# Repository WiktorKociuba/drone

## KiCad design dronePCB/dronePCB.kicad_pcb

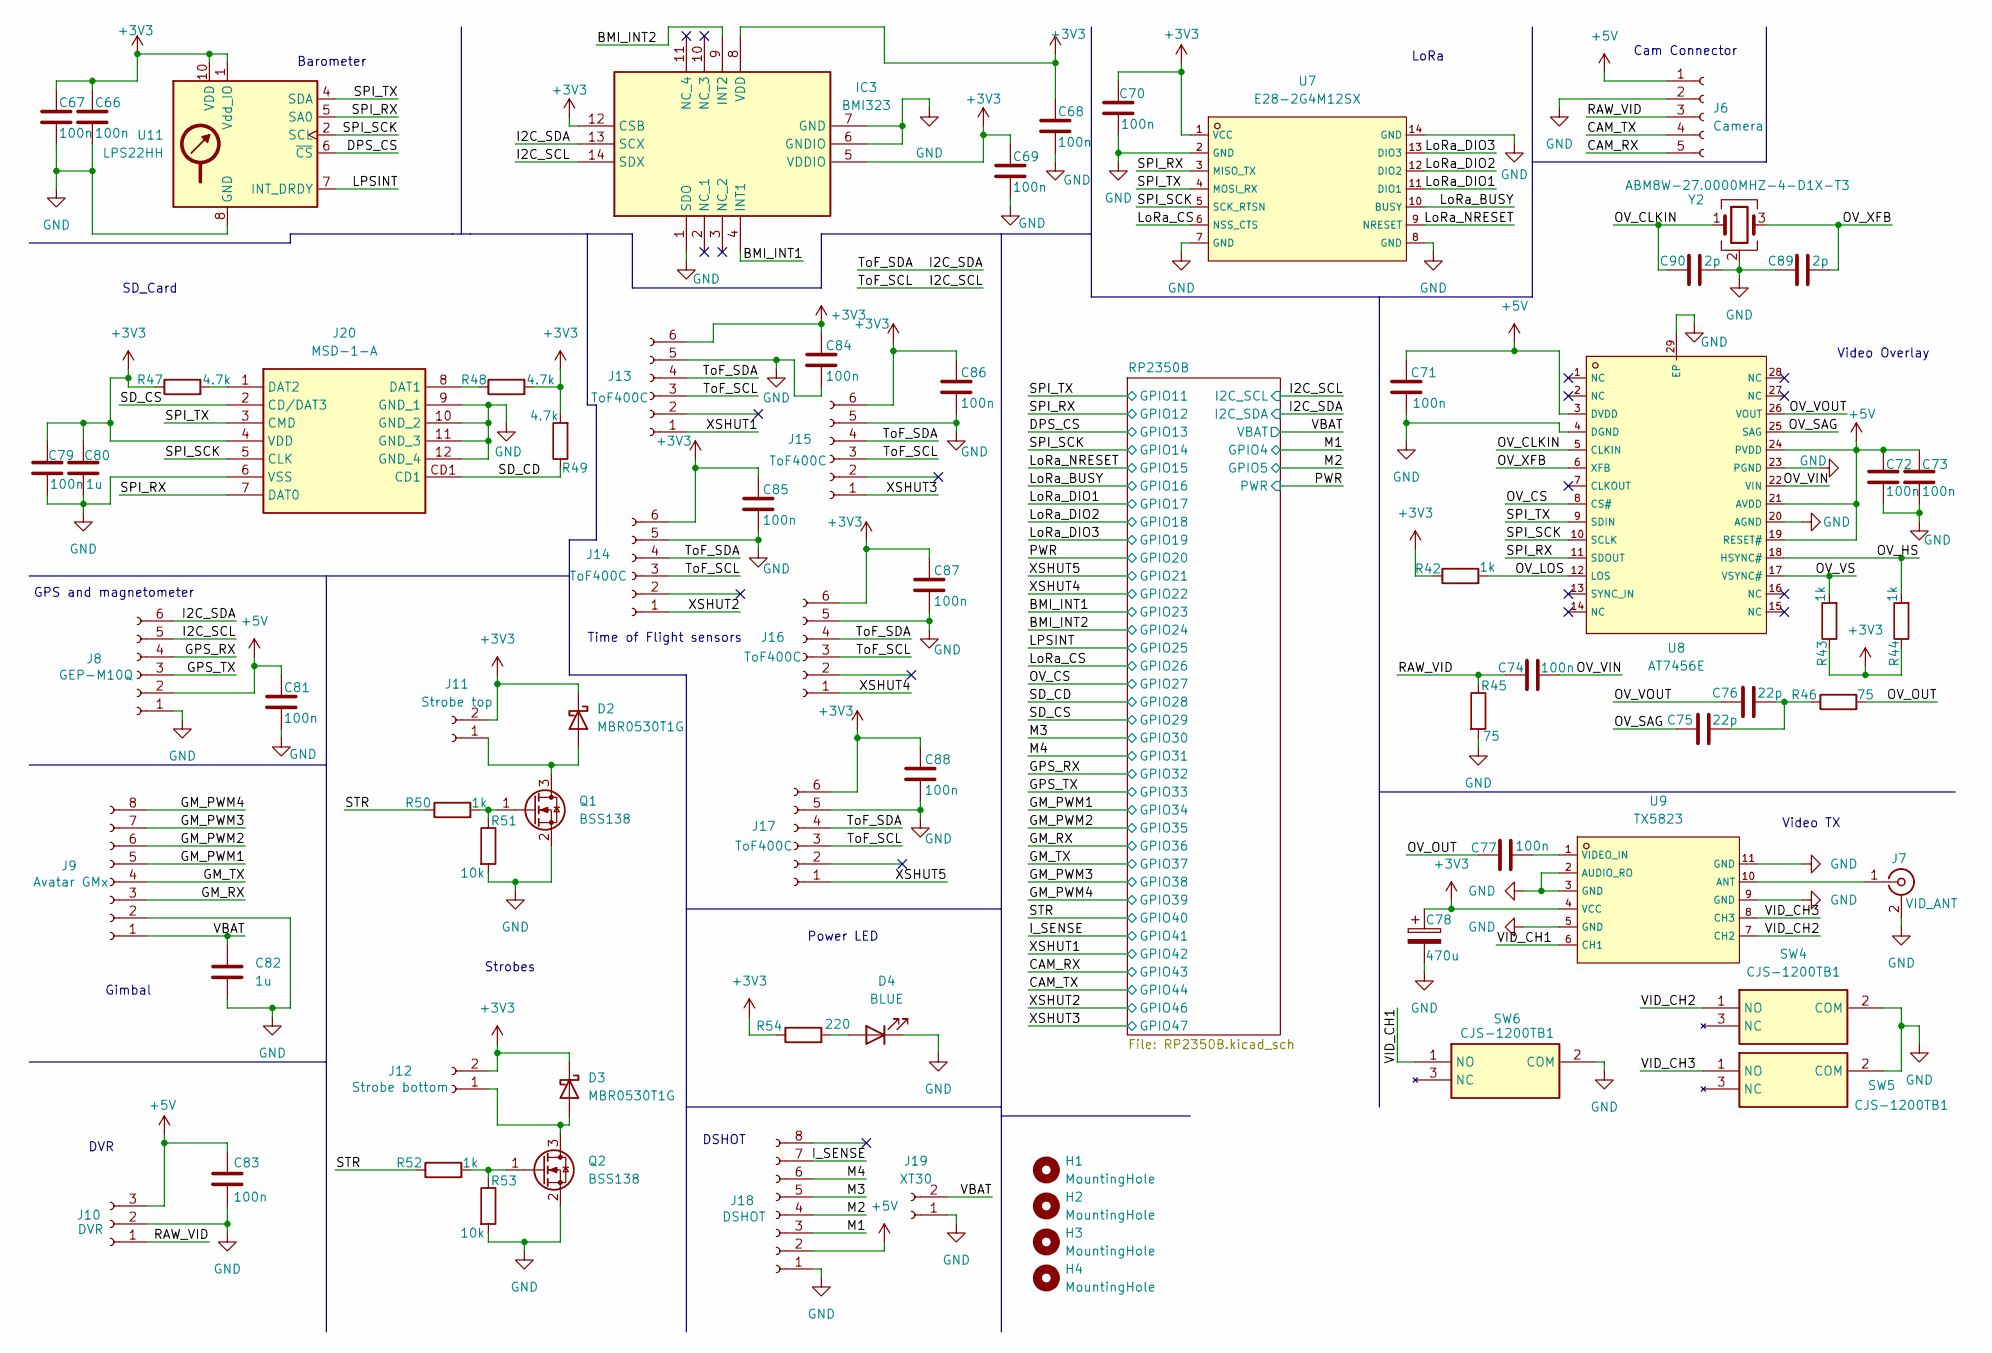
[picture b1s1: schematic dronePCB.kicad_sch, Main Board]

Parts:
C66, C67, C68, C69, C70, C71, C72, C73, C74, C77, C79, C81, C83, C84, C85, C86, C87, C88: 100n; C_0805_2012Metric_Pad1.18x1.45mm_HandSolder; Manufacturer_Part_Number 08056D104KAT2A
C75, C76: 22p; C_0805_2012Metric_Pad1.18x1.45mm_HandSolder; Manufacturer_Part_Number 0805N220J500CT
C78: 470u; CAPAE830X1080N; Manufacturer_Part_Number UCW1C471MNL1GS
C80, C82: 1u; C_0805_2012Metric_Pad1.18x1.45mm_HandSolder; Manufacturer_Part_Number CL21B105KAFNNNG
C89, C90: 2p; C_0805_2012Metric_Pad1.18x1.45mm_HandSolder; Manufacturer_Part_Number 0805N2R0C500CT
D2, D3: MBR0530T1G; D_SOD-123; Manufacturer_Part_Number MBR0530T1G
D4: BLUE; LED_0805_2012Metric_Pad1.15x1.40mm_HandSolder; Manufacturer_Part_Number 150080BS75000
H1, H2, H3, H4: MountingHole; MountingHole_2.2mm_M2; Manufacturer_Part_Number n/a
IC3: BMI323; Mouser Part Number 262-BMI323
J6: Camera; JST_PH_B5B-PH-SM4-TB_1x05-1MP_P2.00mm_Vertical; Manufacturer_Part_Number B5B-PH-SM4-TB(LF)(SN)
J7: VID_ANT; SMA_Amphenol_132134-11_Vertical; Manufacturer_Part_Number n/a
J8: GEP-M10Q; JST_PH_B6B-PH-SM4-TB_1x06-1MP_P2.00mm_Vertical; Manufacturer_Part_Number B6B-PH-SM4-TB(LF)(SN)
J9: Avatar GMx; JST_PH_B8B-PH-SM4-TB_1x08-1MP_P2.00mm_Vertical; Manufacturer_Part_Number B8B-PH-SM4-TBT(LF)(SN)
J10: DVR; JST_PH_B3B-PH-SM4-TB_1x03-1MP_P2.00mm_Vertical; Manufacturer_Part_Number B3B-PH-SM4-TB(LF)(SN)
J11: Strobe top; JST_PH_B2B-PH-SM4-TB_1x02-1MP_P2.00mm_Vertical; Manufacturer_Part_Number B2B-PH-SM4-TB(LF)(SN)
J12: Strobe bottom; JST_PH_B2B-PH-SM4-TB_1x02-1MP_P2.00mm_Vertical; Manufacturer_Part_Number B2B-PH-SM4-TB(LF)(SN)
J13, J14, J15, J16, J17: ToF400C; JST_PH_B6B-PH-SM4-TB_1x06-1MP_P2.00mm_Vertical; Manufacturer_Part_Number B6B-PH-SM4-TB(LF)(SN)
J18: DSHOT; JST_PH_B8B-PH-SM4-TB_1x08-1MP_P2.00mm_Vertical; Manufacturer_Part_Number B8B-PH-SM4-TBT(LF)(SN)
J19: XT30; AMASS_XT30U-F_1x02_P5.0mm_Vertical; Manufacturer_Part_Number XT30U-F AMASS
J20: MSD-1-A; MSD1A; Mouser Part Number 179-MSD-1-A
Q1, Q2: BSS138; SOT-23; Manufacturer_Part_Number BSS138
R42, R43, R44, R50, R52: 1k; R_0805_2012Metric_Pad1.20x1.40mm_HandSolder; Manufacturer_Part_Number CRM0805-FX-1001ELF
R45, R46: 75; R_0805_2012Metric_Pad1.20x1.40mm_HandSolder; Manufacturer_Part_Number CRCW080575R0FKEA
R47, R48, R49: 4.7k; R_0805_2012Metric_Pad1.20x1.40mm_HandSolder; Manufacturer_Part_Number RG2012P-472-B-T5
R51, R53: 10k; R_0805_2012Metric_Pad1.20x1.40mm_HandSolder; Manufacturer_Part_Number CRM0805-FX-1002ELF
R54: 220; R_0805_2012Metric_Pad1.20x1.40mm_HandSolder; Manufacturer_Part_Number CRCW0805220RFKEA
SW4, SW5, SW6: CJS-1200TB1; CJS1200TB1; Mouser Part Number 229-CJS-1200TB1
U7: E28-2G4M12SX; COMM-SMD_E28-2G4M12SX; Manufacturer_Part_Number E28-2G4M12SX; LCSC C17916848
U8: AT7456E; Manufacturer_Part_Number AT7456E; LCSC C82351
U9: TX5823; Manufacturer_Part_Number TX5823; LCSC C2908188
U11: LPS22HH; ST_HLGA-10_2x2mm_P0.5mm_LayoutBorder3x2y; Manufacturer_Part_Number LPS22HBTR
Y2: ABM8W-27.0000MHZ-4-D1X-T3; ABM8W480000MHZ6D1XT3; Manufacturer_Part_Number ABM8W-27.0000MHZ-4-D1X-T3

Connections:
+3V3: C66.1, C67.1, C68.1, C69.1, C70.1, C78.1, C79.1, C80.1, C84.1, C85.1, C86.1, C87.1, C88.1, D2.1 (K), D3.1 (K), IC3.5 (VDDIO), IC3.8 (VDD), IC3.12 (CSB), J11.2, J12.2, J13.6, J14.6, J15.6, J16.6, J17.6, J20.4 (VDD), R42.1, R43.1, R44.1, R47.1, R48.2, R49.2, R54.1, U7.1 (VCC), U9.4 (VCC), U11.1 (Vdd_IO), U11.10 (VDD); also elsewhere on the board
+5V: C71.1, C72.1, C73.1, C81.1, C83.1, J6.1, J8.2, J10.3, J18.2, U8.3 (DVDD), U8.19 (RESET#), U8.21 (AVDD), U8.24 (PVDD); also elsewhere on the board
/BMI_INT1: IC3.4 (INT1); also elsewhere on the board
/BMI_INT2: IC3.9 (INT2); also elsewhere on the board
/CAM_RX: J6.5; also elsewhere on the board
/CAM_TX: J6.4; also elsewhere on the board
/DPS_CS: U11.6 (~CS); also elsewhere on the board
/GM_PWM1: J9.5; also elsewhere on the board
/GM_PWM2: J9.6; also elsewhere on the board
/GM_PWM3: J9.7; also elsewhere on the board
/GM_PWM4: J9.8; also elsewhere on the board
/GM_RX: J9.3; also elsewhere on the board
/GM_TX: J9.4; also elsewhere on the board
/GPS_RX: J8.4; also elsewhere on the board
/GPS_TX: J8.3; also elsewhere on the board
/I2C_SCL: IC3.14 (SDX), J8.5, J13.3, J14.3, J15.3, J16.3, J17.3; also elsewhere on the board
/I2C_SDA: IC3.13 (SCX), J8.6, J13.4, J14.4, J15.4, J16.4, J17.4; also elsewhere on the board
/I_SENSE: J18.7; also elsewhere on the board
/LPSINT: U11.7 (INT_DRDY); also elsewhere on the board
/LoRa_BUSY: U7.10 (BUSY); also elsewhere on the board
/LoRa_CS: U7.6 (NSS_CTS); also elsewhere on the board
/LoRa_DIO1: U7.11 (DIO1); also elsewhere on the board
/LoRa_DIO2: U7.12 (DIO2); also elsewhere on the board
/LoRa_DIO3: U7.13 (DIO3); also elsewhere on the board
/LoRa_NRESET: U7.9 (NRESET); also elsewhere on the board
/M1: J18.3; also elsewhere on the board
/M2: J18.4; also elsewhere on the board
/M3: J18.5; also elsewhere on the board
/M4: J18.6; also elsewhere on the board
/OV_CLKIN: C90.1, U8.5 (CLKIN), Y2.1
/OV_CS: U8.8 (CS#); also elsewhere on the board
/OV_HS: R44.2, U8.18 (HSYNC#)
/OV_LOS: R42.2, U8.12 (LOS)
/OV_OUT: C77.1, R46.2
/OV_SAG: C75.1, U8.25 (SAG)
/OV_VIN: C74.2, U8.22 (VIN)
/OV_VOUT: C76.1, U8.26 (VOUT)
/OV_VS: R43.2, U8.17 (VSYNC#)
/OV_XFB: C89.2, U8.6 (XFB), Y2.3
/RAW_VID: C74.1, J6.3, J10.1, R45.1
/SD_CD: J20.CD1, R49.1; also elsewhere on the board
/SD_CS: J20.2 (CD/DAT3); also elsewhere on the board
/SPI_RX: J20.7 (DAT0), U7.3 (MISO_TX), U8.11 (SDOUT), U11.5 (SA0); also elsewhere on the board
/SPI_SCK: J20.5 (CLK), U7.5 (SCK_RTSN), U8.10 (SCLK), U11.2 (SCL); also elsewhere on the board
/SPI_TX: J20.3 (CMD), U7.4 (MOSI_RX), U8.9 (SDIN), U11.4 (SDA); also elsewhere on the board
/STR: R50.1, R52.1; also elsewhere on the board
/VBAT: C82.1, J9.1, J19.2; also elsewhere on the board
/VID_CH1: SW6.1 (NO), U9.6 (CH1)
/VID_CH2: SW4.1 (NO), U9.7 (CH2)
/VID_CH3: SW5.1 (NO), U9.8 (CH3)
/XSHUT1: J13.1; also elsewhere on the board
/XSHUT2: J14.1; also elsewhere on the board
/XSHUT3: J15.1; also elsewhere on the board
/XSHUT4: J16.1; also elsewhere on the board
/XSHUT5: J17.1; also elsewhere on the board
GND: C66.2, C67.2, C68.2, C69.2, C70.2, C71.2, C72.2, C73.2, C78.2, C79.2, C80.2, C81.2, C82.2, C83.2, C84.2, C85.2, C86.2, C87.2, C88.2, C89.1, C90.2, D4.1 (K), IC3.1 (SDO), IC3.6 (GNDIO), IC3.7 (GND), J6.2, J7.2 (Ext), J8.1, J9.2, J10.2, J13.5, J14.5, J15.5, J16.5, J17.5, J18.1, J19.1, J20.6 (VSS), J20.9 (GND_1), J20.10 (GND_2), J20.11 (GND_3), J20.12 (GND_4), Q1.2 (S), Q2.2 (S), R45.2, R51.2, R53.2, SW4.2 (COM), SW5.2 (COM), SW6.2 (COM), U7.2 (GND), U7.7 (GND), U7.8 (GND), U7.14 (GND), U8.4 (DGND), U8.20 (AGND), U8.23 (PGND), U8.29 (EP), U9.2 (AUDIO_RO), U9.3 (GND), U9.5 (GND), U9.9 (GND), U9.11 (GND), U11.3 (GND), U11.8 (GND), U11.9 (GND), Y2.2 (G), Y2.4 (G); also elsewhere on the board
unnamed: C75.2, C76.2, R46.1
unnamed: D2.2 (A), J11.1, Q1.3 (D)
unnamed: D3.2 (A), J12.1, Q2.3 (D)
unnamed: D4.2 (A), R54.2
unnamed: J7.1 (In), U9.10 (ANT)
unnamed: J20.8 (DAT1), R48.1
unnamed: J20.1 (DAT2), R47.2
unnamed: Q1.1 (G), R50.2, R51.1
unnamed: Q2.1 (G), R52.2, R53.1
unnamed: C77.2, U9.1 (VIDEO_IN)

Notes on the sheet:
Video Overlay
Strobes
DVR
Gimbal
GPS and magnetometer
Power LED
Time of Flight sensors
LoRa
Cam Connector
Barometer
SD_Card
DSHOT
Video TX

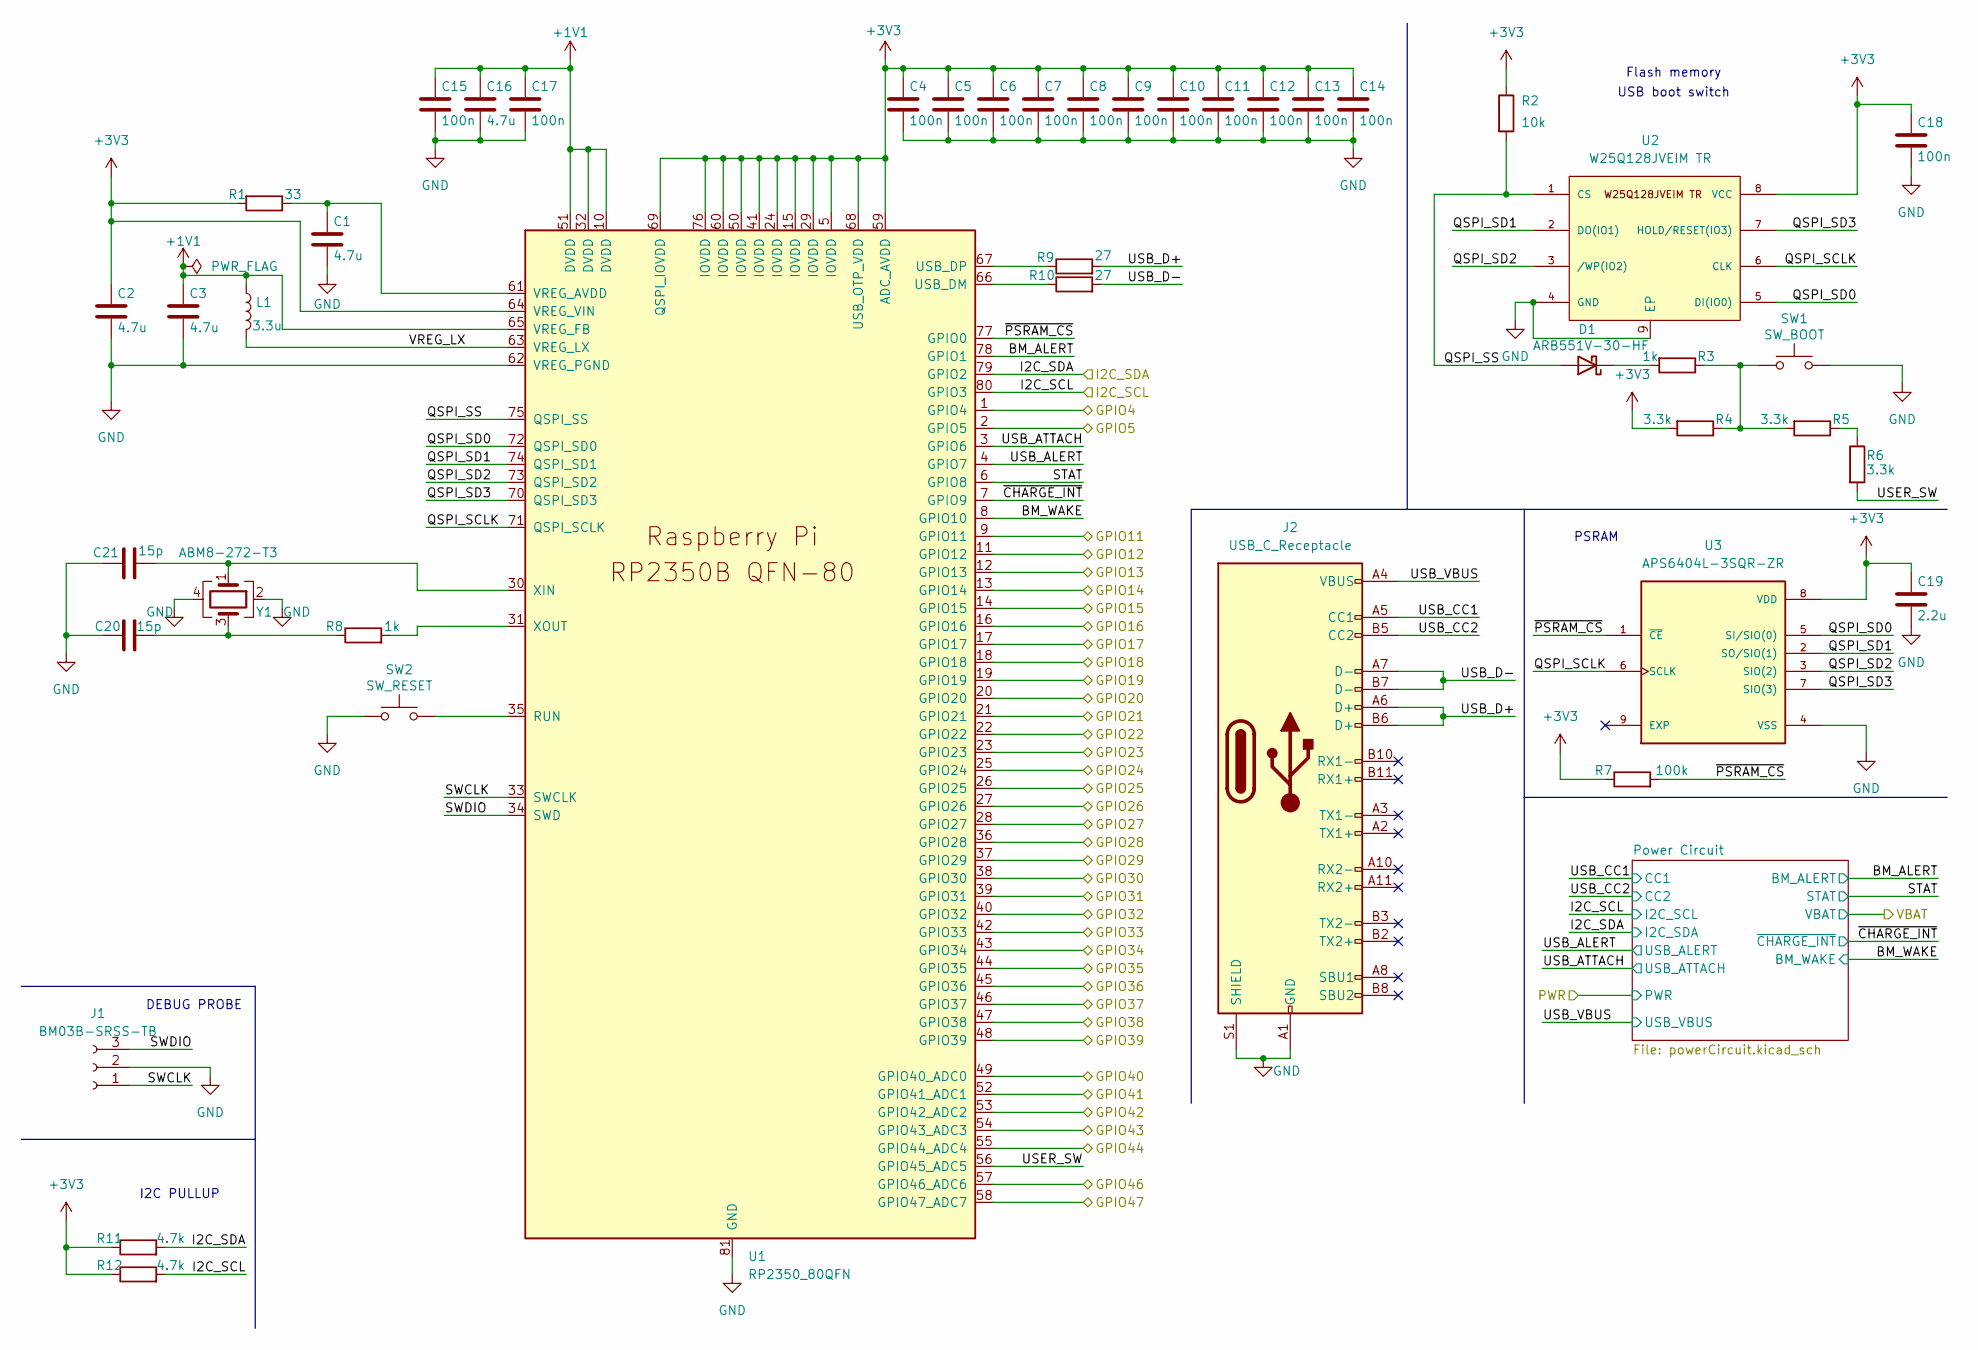
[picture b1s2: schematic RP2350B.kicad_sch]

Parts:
C1, C16: 4.7u; C_0805_2012Metric_Pad1.18x1.45mm_HandSolder; Manufacturer_Part_Number CL21A475KPFNNNF
C2, C3: 4.7u; C_0402_1005Metric_Pad0.74x0.62mm_HandSolder; Manufacturer_Part_Number CL05A475KQ5NRNC
C4, C5, C6, C7, C8, C9, C10, C11, C12, C13, C14, C15, C17, C18: 100n; C_0805_2012Metric_Pad1.18x1.45mm_HandSolder; Manufacturer_Part_Number 08056D104KAT2A
C19: 2.2u; C_0805_2012Metric_Pad1.18x1.45mm_HandSolder; Manufacturer_Part_Number CL21B225KPFNNNE
C20, C21: 15p; C_0805_2012Metric_Pad1.18x1.45mm_HandSolder; Manufacturer_Part_Number C0805C150K1HACTU
D1: ARB551V-30-HF; D_SOD-323_HandSoldering; Manufacturer_Part_Number ARB551V-30-HF
J1: BM03B-SRSS-TB; JST_SH_BM03B-SRSS-TB_1x03-1MP_P1.00mm_Vertical; Manufacturer_Part_Number BM03B-SRSS-TB
J2: USB_C_Receptacle; USB_C_Receptacle_Amphenol_12401610E4-2A; Manufacturer_Part_Number 12401610E4#2A
L1: 3.3u; AOTAB201610S3R3101T; Manufacturer_Part_Number AOTA-B201610S3R3-101-T
R1: 33; R_0805_2012Metric_Pad1.20x1.40mm_HandSolder; Manufacturer_Part_Number CRCW080533R0JNEA
R2: 10k; R_0805_2012Metric_Pad1.20x1.40mm_HandSolder; Manufacturer_Part_Number CRM0805-FX-1002ELF
R3, R8: 1k; R_0805_2012Metric_Pad1.20x1.40mm_HandSolder; Manufacturer_Part_Number CRM0805-FX-1001ELF
R4, R5, R6: 3.3k; R_0805_2012Metric_Pad1.20x1.40mm_HandSolder; Manufacturer_Part_Number SG73S2ARTTD3301F
R7: 100k; R_0805_2012Metric_Pad1.20x1.40mm_HandSolder; Manufacturer_Part_Number CR0805AFX-1003EAS
R9, R10: 27; R_0805_2012Metric_Pad1.20x1.40mm_HandSolder; Manufacturer_Part_Number CRCW080527R0FKEA
R11, R12: 4.7k; R_0805_2012Metric_Pad1.20x1.40mm_HandSolder; Manufacturer_Part_Number RG2012P-472-B-T5
SW1: SW_BOOT; SW_Push_1P1T_NO_Vertical_Wuerth_434133025816; Manufacturer_Part_Number 434133025816
SW2: SW_RESET; SW_Push_1P1T_NO_Vertical_Wuerth_434133025816; Manufacturer_Part_Number 434133025816
U1: RP2350_80QFN; RP2350B; Manufacturer_Part_Number SC1510(13)-A4
U2: W25Q128JVEIM TR; SON127P800X600X80-9N-D; Manufacturer_Part_Number W25Q128JVEIM TR
U3: APS6404L-3SQR-ZR; PSON50P200X300X50-9N; PARTREV 2.3
Y1: ABM8-272-T3; ABM8272T3; Manufacturer_Part_Number ABM8-272-T3

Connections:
+1V1: C3.1, C15.1, C16.1, C17.1, L1.1, U1.10 (DVDD), U1.32 (DVDD), U1.51 (DVDD), U1.65 (VREG_FB)
+3V3: C2.1, C4.1, C5.1, C6.1, C7.1, C8.1, C9.1, C10.1, C11.1, C12.1, C13.1, C14.1, C18.1, C19.1, R1.2, R2.1, R4.2, R7.1, R11.1, R12.1, U1.5 (IOVDD), U1.15 (IOVDD), U1.24 (IOVDD), U1.29 (IOVDD), U1.41 (IOVDD), U1.50 (IOVDD), U1.59 (ADC_AVDD), U1.60 (IOVDD), U1.64 (VREG_VIN), U1.68 (USB_OTP_VDD), U1.69 (QSPI_IOVDD), U1.76 (IOVDD), U2.8 (VCC), U3.8 (VDD); also elsewhere on the board
/BMI_INT1: U1.23 (GPIO23); also elsewhere on the board
/BMI_INT2: U1.25 (GPIO24); also elsewhere on the board
/CAM_RX: U1.54 (GPIO43_ADC3); also elsewhere on the board
/CAM_TX: U1.55 (GPIO44_ADC4); also elsewhere on the board
/DPS_CS: U1.12 (GPIO13); also elsewhere on the board
/GM_PWM1: U1.43 (GPIO34); also elsewhere on the board
/GM_PWM2: U1.44 (GPIO35); also elsewhere on the board
/GM_PWM3: U1.47 (GPIO38); also elsewhere on the board
/GM_PWM4: U1.48 (GPIO39); also elsewhere on the board
/GM_RX: U1.45 (GPIO36); also elsewhere on the board
/GM_TX: U1.46 (GPIO37); also elsewhere on the board
/GPS_RX: U1.40 (GPIO32); also elsewhere on the board
/GPS_TX: U1.42 (GPIO33); also elsewhere on the board
/I2C_SCL: R12.2, U1.80 (GPIO3); also elsewhere on the board
/I2C_SDA: R11.2, U1.79 (GPIO2); also elsewhere on the board
/I_SENSE: U1.52 (GPIO41_ADC1); also elsewhere on the board
/LPSINT: U1.26 (GPIO25); also elsewhere on the board
/LoRa_BUSY: U1.16 (GPIO16); also elsewhere on the board
/LoRa_CS: U1.27 (GPIO26); also elsewhere on the board
/LoRa_DIO1: U1.17 (GPIO17); also elsewhere on the board
/LoRa_DIO2: U1.18 (GPIO18); also elsewhere on the board
/LoRa_DIO3: U1.19 (GPIO19); also elsewhere on the board
/LoRa_NRESET: U1.14 (GPIO15); also elsewhere on the board
/M1: U1.1 (GPIO4); also elsewhere on the board
/M2: U1.2 (GPIO5); also elsewhere on the board
/M3: U1.38 (GPIO30); also elsewhere on the board
/M4: U1.39 (GPIO31); also elsewhere on the board
/OV_CS: U1.28 (GPIO27); also elsewhere on the board
/PWR: U1.20 (GPIO20); also elsewhere on the board
/RP2350B/BM_ALERT: U1.78 (GPIO1); also elsewhere on the board
/RP2350B/BM_WAKE: U1.8 (GPIO10); also elsewhere on the board
/RP2350B/QSPI_SCLK: U1.71 (QSPI_SCLK), U2.6 (CLK), U3.6 (SCLK)
/RP2350B/QSPI_SD0: U1.72 (QSPI_SD0), U2.5 (DI(IO0)), U3.5 (SI/SIO(0))
/RP2350B/QSPI_SD1: U1.74 (QSPI_SD1), U2.2 (DO(IO1)), U3.2 (SO/SIO(1))
/RP2350B/QSPI_SD2: U1.73 (QSPI_SD2), U2.3 (/WP(IO2)), U3.3 (SIO(2))
/RP2350B/QSPI_SD3: U1.70 (QSPI_SD3), U2.7 (HOLD/RESET(IO3)), U3.7 (SIO(3))
/RP2350B/QSPI_SS: D1.2 (A), R2.2, U1.75 (QSPI_SS), U2.1 (CS)
/RP2350B/STAT: U1.6 (GPIO8); also elsewhere on the board
/RP2350B/SWCLK: J1.1, U1.33 (SWCLK)
/RP2350B/SWDIO: J1.3, U1.34 (SWD)
/RP2350B/USB_ALERT: U1.4 (GPIO7); also elsewhere on the board
/RP2350B/USB_ATTACH: U1.3 (GPIO6); also elsewhere on the board
/RP2350B/USB_CC1: J2.A5 (CC1); also elsewhere on the board
/RP2350B/USB_CC2: J2.B5 (CC2); also elsewhere on the board
/RP2350B/USB_D+: J2.A6 (D+), J2.B6 (D+), R9.2
/RP2350B/USB_D-: J2.A7 (D-), J2.B7 (D-), R10.2
/RP2350B/USB_VBUS: J2.A4 (VBUS), J2.A9 (VBUS), J2.B4 (VBUS), J2.B9 (VBUS); also elsewhere on the board
/RP2350B/USER_SW: R6.2, U1.56 (GPIO45_ADC5)
/RP2350B/VREG_LX: L1.2, U1.63 (VREG_LX)
/RP2350B/~CHARGE_INT: U1.7 (GPIO9); also elsewhere on the board
/RP2350B/~PSRAM_CS: R7.2, U1.77 (GPIO0), U3.1 (~CE)
/SD_CD: U1.36 (GPIO28); also elsewhere on the board
/SD_CS: U1.37 (GPIO29); also elsewhere on the board
/SPI_RX: U1.11 (GPIO12); also elsewhere on the board
/SPI_SCK: U1.13 (GPIO14); also elsewhere on the board
/SPI_TX: U1.9 (GPIO11); also elsewhere on the board
/STR: U1.49 (GPIO40_ADC0); also elsewhere on the board
/XSHUT1: U1.53 (GPIO42_ADC2); also elsewhere on the board
/XSHUT2: U1.57 (GPIO46_ADC6); also elsewhere on the board
/XSHUT3: U1.58 (GPIO47_ADC7); also elsewhere on the board
/XSHUT4: U1.22 (GPIO22); also elsewhere on the board
/XSHUT5: U1.21 (GPIO21); also elsewhere on the board
GND: C1.2, C2.2, C3.2, C4.2, C5.2, C6.2, C7.2, C8.2, C9.2, C10.2, C11.2, C12.2, C13.2, C14.2, C15.2, C16.2, C17.2, C18.2, C19.2, C20.1, C21.1, J1.2, J2.A1 (GND), J2.A12 (GND), J2.B1 (GND), J2.B12 (GND), J2.S1 (SHIELD), SW1.2, SW2.1, U1.62 (VREG_PGND), U1.81 (GND), U2.4 (GND), U2.9 (GND), U3.4 (VSS), Y1.2, Y1.4; also elsewhere on the board
unnamed: C20.2, R8.1, Y1.3
unnamed: D1.1 (K), R3.2
unnamed: R3.1, R4.1, R5.2, SW1.1
unnamed: R5.1, R6.1
unnamed: SW2.2, U1.35 (RUN)
unnamed: R10.1, U1.66 (USB_DM)
unnamed: R9.1, U1.67 (USB_DP)
unnamed: C1.1, R1.1, U1.61 (VREG_AVDD)
unnamed: C21.2, U1.30 (XIN), Y1.1
unnamed: R8.2, U1.31 (XOUT)

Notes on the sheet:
PSRAM
I2C PULLUP
DEBUG PROBE
Flash memory
USB boot switch

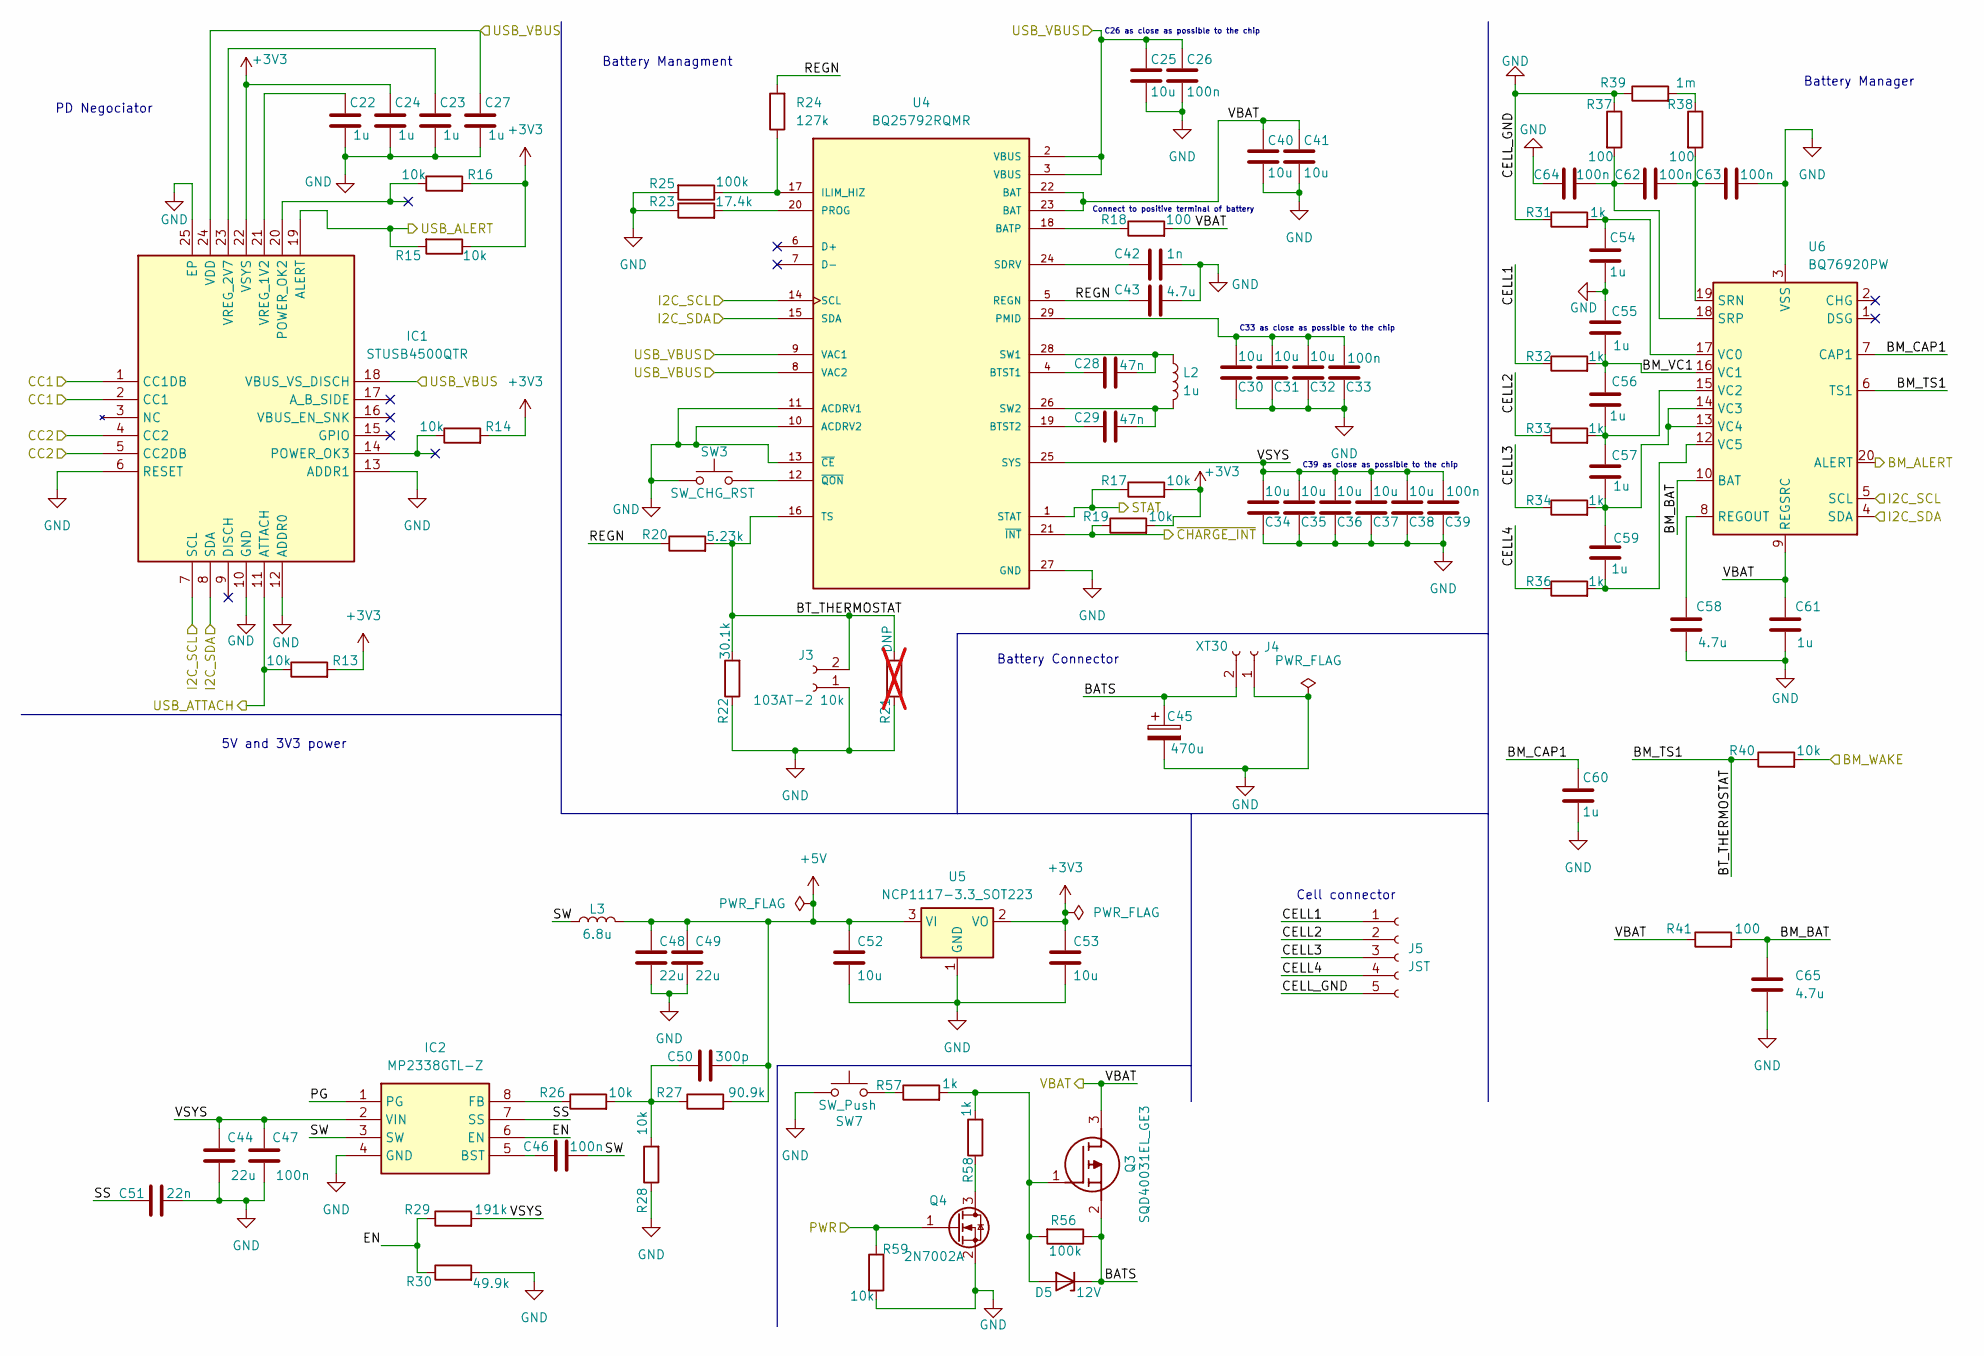
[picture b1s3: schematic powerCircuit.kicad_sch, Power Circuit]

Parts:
C22, C23, C24, C27, C54, C55, C56, C57, C59, C60, C61: 1u; C_0805_2012Metric_Pad1.18x1.45mm_HandSolder; Manufacturer_Part_Number CL21B105KAFNNNG
C25, C30, C31, C32, C34, C35, C36, C37, C38, C40, C41, C52, C53: 10u; C_0805_2012Metric_Pad1.18x1.45mm_HandSolder; Manufacturer_Part_Number CL21A106KOQNNNE
C26, C33, C39, C46, C47, C62, C63, C64: 100n; C_0805_2012Metric_Pad1.18x1.45mm_HandSolder; Manufacturer_Part_Number 08056D104KAT2A
C28, C29: 47n; C_0805_2012Metric_Pad1.18x1.45mm_HandSolder; Manufacturer_Part_Number KGM21NR71C473KT
C42: 1n; C_0805_2012Metric_Pad1.18x1.45mm_HandSolder; Manufacturer_Part_Number CL21B102KBCNNNC
C43, C58, C65: 4.7u; C_0805_2012Metric_Pad1.18x1.45mm_HandSolder; Manufacturer_Part_Number CL21A475KPFNNNF
C44, C48, C49: 22u; C_0805_2012Metric_Pad1.18x1.45mm_HandSolder; Manufacturer_Part_Number CL21A226KQCLRNC
C45: 470u; CAPAE830X1080N; Manufacturer_Part_Number UCW1C471MNL1GS
C50: 300p; C_0805_2012Metric_Pad1.18x1.45mm_HandSolder; Manufacturer_Part_Number 0805N301J500CT
C51: 22n; C_0805_2012Metric_Pad1.18x1.45mm_HandSolder; Manufacturer_Part_Number CC0805KRX7R7BB223
D5: 12V; SOD3716X135N; Manufacturer_Part_Number MMSZ4699T1G
IC1: STUSB4500QTR; Mouser Part Number 511-STUSB4500QTR
IC2: MP2338GTL-Z; MP2338GTLZ; Mouser Part Number 946-MP2338GTL-Z
J3: 103AT-2 10k; JST_PH_B2B-PH-SM4-TB_1x02-1MP_P2.00mm_Vertical; Manufacturer_Part_Number B2B-PH-SM4-TB(LF)(SN)
J4: XT30; AMASS_XT30U-F_1x02_P5.0mm_Vertical; Manufacturer_Part_Number XT30U-F AMASS
J5: JST; JST_PH_B5B-PH-SM4-TB_1x05-1MP_P2.00mm_Vertical; Manufacturer_Part_Number B5B-PH-SM4-TB(LF)(SN)
L2: 1u; AMPLH7020S-1R0MT; Manufacturer_Part_Number AMPLH7020S-1R0MT
L3: 6.8u; AMPLH5030S-6R8MT; Manufacturer_Part_Number AMPLH5030S-6R8MT
Q3: SQD40031EL_GE3; Mouser Part Number 78-SQD40031EL_GE3
Q4: 2N7002A; SOT-23; Manufacturer_Part_Number 2N7002A
R13, R14, R15, R16, R17, R19, R26, R28, R40, R59: 10k; R_0805_2012Metric_Pad1.20x1.40mm_HandSolder; Manufacturer_Part_Number CRM0805-FX-1002ELF
R18, R37, R38, R41: 100; R_0805_2012Metric_Pad1.20x1.40mm_HandSolder; Manufacturer_Part_Number RMCA0805FT100R-HP
R20: 5.23k; R_0805_2012Metric_Pad1.20x1.40mm_HandSolder; Manufacturer_Part_Number RT0805FRE075K23L
R21: DNP; R_0805_2012Metric_Pad1.20x1.40mm_HandSolder; Manufacturer_Part_Number n/a; not fitted
R22: 30.1k; R_0805_2012Metric_Pad1.20x1.40mm_HandSolder; Manufacturer_Part_Number RT0805DRE0730K1L
R23: 17.4k; R_0805_2012Metric_Pad1.20x1.40mm_HandSolder; Manufacturer_Part_Number CR0805-FX-1742ELF
R24: 127k; R_0805_2012Metric_Pad1.20x1.40mm_HandSolder; Manufacturer_Part_Number RT0805FRE07127KL
R25, R56: 100k; R_0805_2012Metric_Pad1.20x1.40mm_HandSolder; Manufacturer_Part_Number CR0805AFX-1003EAS
R27: 90.9k; R_0805_2012Metric_Pad1.20x1.40mm_HandSolder; Manufacturer_Part_Number RT0805FRE0790K9L
R29: 191k; R_0805_2012Metric_Pad1.20x1.40mm_HandSolder; Manufacturer_Part_Number RT0805FRE07191KL
R30: 49.9k; R_0805_2012Metric_Pad1.20x1.40mm_HandSolder; Manufacturer_Part_Number RT0805FRD0749K9L
R31, R32, R33, R34, R36, R57, R58: 1k; R_0805_2012Metric_Pad1.20x1.40mm_HandSolder; Manufacturer_Part_Number CRM0805-FX-1001ELF
R39: 1m; R_0805_2012Metric_Pad1.20x1.40mm_HandSolder; Manufacturer_Part_Number CSSH0805FT1L00
SW3: SW_CHG_RST; SW_Push_1P1T_NO_Vertical_Wuerth_434133025816; Manufacturer_Part_Number 434133025816
SW7: SW_Push; SW_Push_1P1T-MP_NO_Horizontal_Alps_SKRTLAE010; Manufacturer_Part_Number SKRTLAE010
U4: BQ25792RQMR; PARTREV 11/2019
U5: NCP1117-3.3_SOT223; SOT-223-3_TabPin2; Manufacturer_Part_Number NCP1117ST33T3G
U6: BQ76920PW; TSSOP-20_4.4x6.5mm_P0.65mm; Manufacturer_Part_Number BQ7692000PW

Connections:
+3V3: C24.1, C53.1, IC1.22 (VSYS), R13.2, R14.2, R15.1, R16.2, R17.2, R19.2, U5.2 (VO); also elsewhere on the board
+5V: C48.1, C49.1, C50.2, C52.1, L3.2, R27.2, U5.3 (VI); also elsewhere on the board
/I2C_SCL: IC1.7 (SCL), U4.14 (SCL), U6.5 (SCL); also elsewhere on the board
/I2C_SDA: IC1.8 (SDA), U4.15 (SDA), U6.4 (SDA); also elsewhere on the board
/PWR: Q4.1 (G), R59.1; also elsewhere on the board
/RP2350B/BM_ALERT: U6.20 (ALERT); also elsewhere on the board
/RP2350B/BM_WAKE: R40.2; also elsewhere on the board
/RP2350B/Power Circuit/BATS: C45.1, D5.1 (K), J4.2 (Pin_1), Q3.2 (S), R56.1
/RP2350B/Power Circuit/BM_BAT: C65.1, R41.2, U6.10 (BAT)
/RP2350B/Power Circuit/BM_CAP1: C60.1, U6.7 (CAP1)
/RP2350B/Power Circuit/BM_TS1: J3.2, R20.2, R21.2, R22.2, R40.1, U4.16 (TS), U6.6 (TS1)
/RP2350B/Power Circuit/BM_VC1: C55.2, C56.1, R32.2, U6.16 (VC1)
/RP2350B/Power Circuit/CELL1: J5.1, R32.1
/RP2350B/Power Circuit/CELL2: J5.2, R33.1
/RP2350B/Power Circuit/CELL3: J5.3, R34.1
/RP2350B/Power Circuit/CELL4: J5.4, R36.1
/RP2350B/Power Circuit/EN: IC2.6 (EN), R29.1, R30.1
/RP2350B/Power Circuit/PG: IC2.1 (PG)
/RP2350B/Power Circuit/REGN: C43.1, R20.1, R24.2, U4.5 (REGN)
/RP2350B/Power Circuit/SS: C51.1, IC2.7 (SS)
/RP2350B/Power Circuit/SW: C46.2, IC2.3 (SW), L3.1
/RP2350B/Power Circuit/VSYS: C34.2, C35.2, C36.2, C37.2, C38.2, C39.2, C44.1, C47.1, IC2.2 (VIN), R29.2, U4.25 (SYS)
/RP2350B/STAT: R17.1, U4.1 (STAT); also elsewhere on the board
/RP2350B/USB_ALERT: IC1.19 (ALERT), R15.2; also elsewhere on the board
/RP2350B/USB_ATTACH: IC1.11 (ATTACH), R13.1; also elsewhere on the board
/RP2350B/USB_CC1: IC1.1 (CC1DB), IC1.2 (CC1); also elsewhere on the board
/RP2350B/USB_CC2: IC1.4 (CC2), IC1.5 (CC2DB); also elsewhere on the board
/RP2350B/USB_VBUS: C25.1, C26.1, C27.1, IC1.18 (VBUS_VS_DISCH), IC1.24 (VDD), U4.2 (VBUS), U4.3 (VBUS), U4.8 (VAC2), U4.9 (VAC1); also elsewhere on the board
/RP2350B/~CHARGE_INT: R19.1, U4.21 (~INT); also elsewhere on the board
/VBAT: C40.1, C41.1, C61.1, Q3.3 (D), R18.2, R41.1, U4.22 (BAT), U4.23 (BAT), U6.9 (REGSRC); also elsewhere on the board
GND: C22.2, C23.2, C24.2, C25.2, C26.2, C27.2, C30.1, C31.1, C32.1, C33.1, C34.1, C35.1, C36.1, C37.1, C38.1, C39.1, C40.2, C41.2, C42.2, C43.2, C44.2, C45.2, C47.2, C48.2, C49.2, C51.2, C52.2, C53.2, C54.2, C55.1, C58.2, C60.2, C61.2, C63.2, C64.1, C65.2, IC1.6 (RESET), IC1.10 (GND), IC1.12 (ADDR0), IC1.13 (ADDR1), IC1.25 (EP), IC2.4 (GND), J3.1, J4.1 (Pin_2), J5.5, Q4.2 (S), R21.1, R22.1, R23.1, R25.2, R28.1, R30.2, R31.1, R37.1, R39.1, R59.2, SW3.1, SW7.1, U4.10 (ACDRV2), U4.11 (ACDRV1), U4.13 (~CE), U4.27 (GND), U5.1 (GND), U6.3 (VSS); also elsewhere on the board
unnamed: C50.1, R26.2, R27.1, R28.2
unnamed: D5.2 (A), Q3.1 (G), R56.2, R57.2, R58.2
unnamed: C22.1, IC1.21 (VREG_1V2)
unnamed: C23.1, IC1.23 (VREG_2V7)
unnamed: C46.1, IC2.5 (BST)
unnamed: IC2.8 (FB), R26.1
unnamed: Q4.3 (D), R58.1
unnamed: R38.1, R39.2
unnamed: R57.1, SW7.2
unnamed: R18.1, U4.18 (BATP)
unnamed: C28.1, U4.4 (BTST1)
unnamed: C29.1, U4.19 (BTST2)
unnamed: R24.1, R25.1, U4.17 (ILIM_HIZ)
unnamed: C30.2, C31.2, C32.2, C33.2, U4.29 (PMID)
unnamed: R23.2, U4.20 (PROG)
unnamed: C42.1, U4.24 (SDRV)
unnamed: C28.2, L2.1, U4.28 (SW1)
unnamed: C29.2, L2.2, U4.26 (SW2)
unnamed: SW3.2, U4.12 (~QON)
unnamed: C58.1, U6.8 (REGOUT)
unnamed: C62.2, C63.1, R38.2, U6.19 (SRN)
unnamed: C62.1, C64.2, R37.2, U6.18 (SRP)
unnamed: C54.1, R31.2, U6.17 (VC0)
unnamed: C56.2, C57.1, R33.2, U6.15 (VC2)
unnamed: C57.2, C59.1, R34.2, U6.13 (VC4), U6.14 (VC3)
unnamed: C59.2, R36.2, U6.12 (VC5)

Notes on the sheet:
C39 as close as possible to the chip
Battery Managment
C26 as close as possible to the chip
Cell connector
Battery Connector
Battery Manager
C33 as close as possible to the chip
PD Negociator
Connect to positive terminal of battery
5V and 3V3 power
